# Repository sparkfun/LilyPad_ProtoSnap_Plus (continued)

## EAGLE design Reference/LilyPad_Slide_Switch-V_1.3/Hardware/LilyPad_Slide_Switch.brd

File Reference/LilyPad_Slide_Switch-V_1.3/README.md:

SparkFun LilyPad Slide Switch 
========================================

[*SparkFun LilyPad Slide Switch (DEV-09350)*](https://www.sparkfun.com/products/9350)

This is a simple slide switch for the LilyPad. 
Use it as a simple ON/OFF switch, or to control LEDs, buzzers, sensors, etc. The swtiches on each board are rated for 4 volts at 300mA, but will work at 5 volts with a reduction in current.

Repository Contents
-------------------

* **/Hardware** - Eagle design files (.brd, .sch)
* **/Production** - Production panel files (.brd)

Documentation
--------------

* **[Hookup Guide](https://learn.sparkfun.com/tutorials/ldk-experiment-3-buttons-and-switches)** - Basic hookup guide for the LilyPad Switch.
* **[SparkFun Fritzing repo](https://github.com/sparkfun/Fritzing_Parts)** - Fritzing diagrams for SparkFun products.
* **[SparkFun 3D Model repo](https://github.com/sparkfun/3D_Models)** - 3D models of SparkFun products. 

License Information
-------------------
This product is _**open source**_! 

The **hardware** is released under [Creative Commons ShareAlike 4.0 International](https://creativecommons.org/licenses/by-sa/4.0/).

Please use, reuse, and modify these files as you see fit. Please maintain attribution to SparkFun Electronics and release anything derivative under the same license.

Distributed as-is; no warranty is given.

- Your friends at SparkFun.

_Note: A portion of this sale is given back to Dr. Leah Buechley for continued development and education of e-textiles._

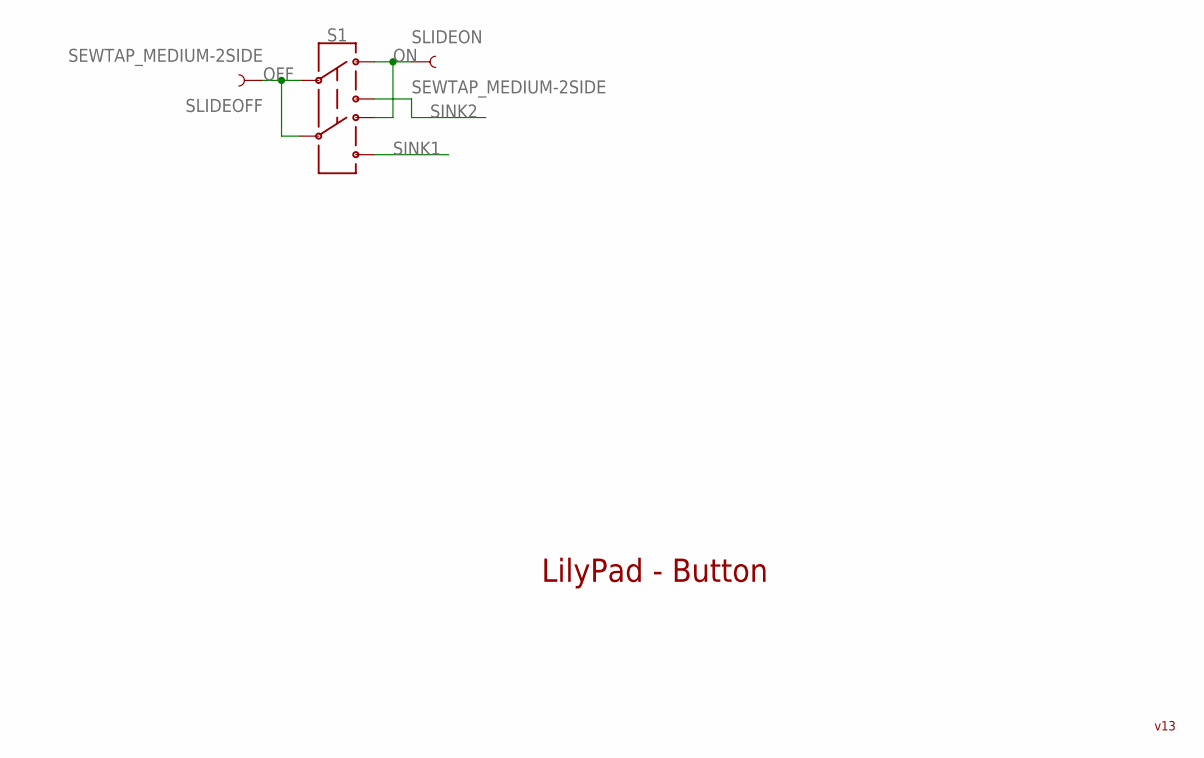
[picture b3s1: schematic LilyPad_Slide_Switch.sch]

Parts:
S1: SWITCH-DPDT-SMD-AYZ0202; SWITCH_DPDT_SMD_AYZ0202
SLIDEOFF: SEWTAP_MEDIUM-2SIDE; PETAL-MEDIUM-2SIDE
SLIDEON: SEWTAP_MEDIUM-2SIDE; PETAL-MEDIUM-2SIDE

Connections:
OFF: S1.2, S1.5, SLIDEOFF.1
ON: S1.1, S1.4, SLIDEON.1
SINK1: S1.6
SINK2: S1.3

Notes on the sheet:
LilyPad - Button
v13

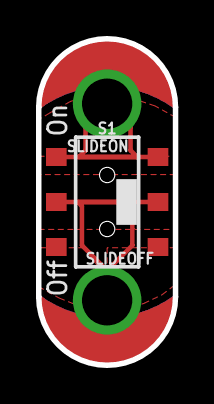
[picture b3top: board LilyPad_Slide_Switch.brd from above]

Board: 2 copper layers, 7.6 x 18.1 mm, 3 parts (0 on the bottom side), 2 nets.

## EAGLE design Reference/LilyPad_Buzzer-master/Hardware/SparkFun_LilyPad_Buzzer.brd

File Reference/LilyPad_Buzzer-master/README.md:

LilyPad Buzzer
========================================

[*LilyPad Buzzer (DEV-08463)*](https://www.sparkfun.com/products/8463)

This is a small buzzer for the LilyPad system. 
Use 2 I/O pins on the LilyPad main board and create different noises based on the different frequency of I/O toggling. 
Loud enough to hear inside a pocket but not obtrusively loud.

Repository Contents
-------------------

* **/Hardware** - Eagle design files (.brd, .sch)
* **/Production** - Production panel files (.brd)

Documentation
--------------
* **[SparkFun Fritzing repo](https://github.com/sparkfun/Fritzing_Parts)** - Fritzing diagrams for SparkFun products.
* **[SparkFun 3D Model repo](https://github.com/sparkfun/3D_Models)** - 3D models of SparkFun products. 

License Information
-------------------
This product is _**open source**_! 

The **hardware** is released under [Creative Commons ShareAlike 4.0 International](https://creativecommons.org/licenses/by-sa/4.0/).

Please use, reuse, and modify these files as you see fit. Please maintain attribution to SparkFun Electronics and release anything derivative under the same license.

Distributed as-is; no warranty is given.

- Your friends at SparkFun.

_**Note**: A portion of this sale is given back to Dr. Leah Buechley for continued development and education of e-textiles._

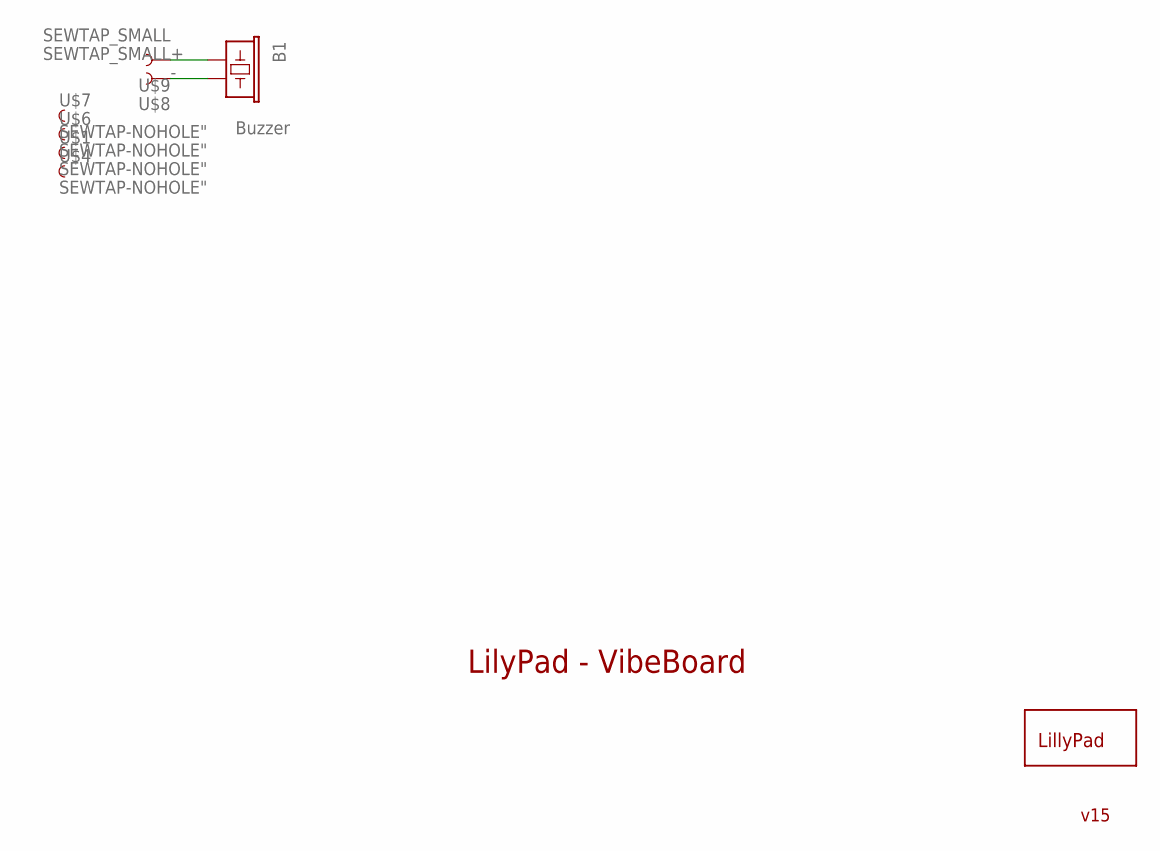
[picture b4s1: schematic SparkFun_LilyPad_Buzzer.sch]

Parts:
B1: Buzzer; BUZZER-CCV
U$1, U$4, U$6, U$7: SEWTAP-NOHOLE"; PETAL-NOHOLE
U$2: LOGO-LPLP; LOGO-LILYPAD
U$8, U$9: SEWTAP_SMALL; PETAL-SMALL

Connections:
+: B1.+ (1), U$9.1
-: B1.- (2), U$8.1

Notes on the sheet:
LilyPad - VibeBoard
v15

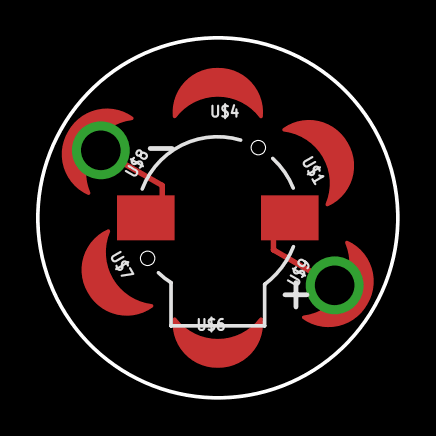
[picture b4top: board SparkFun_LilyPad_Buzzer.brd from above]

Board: 2 copper layers, 20.0 x 20.0 mm, 8 parts (1 on the bottom side), 2 nets.

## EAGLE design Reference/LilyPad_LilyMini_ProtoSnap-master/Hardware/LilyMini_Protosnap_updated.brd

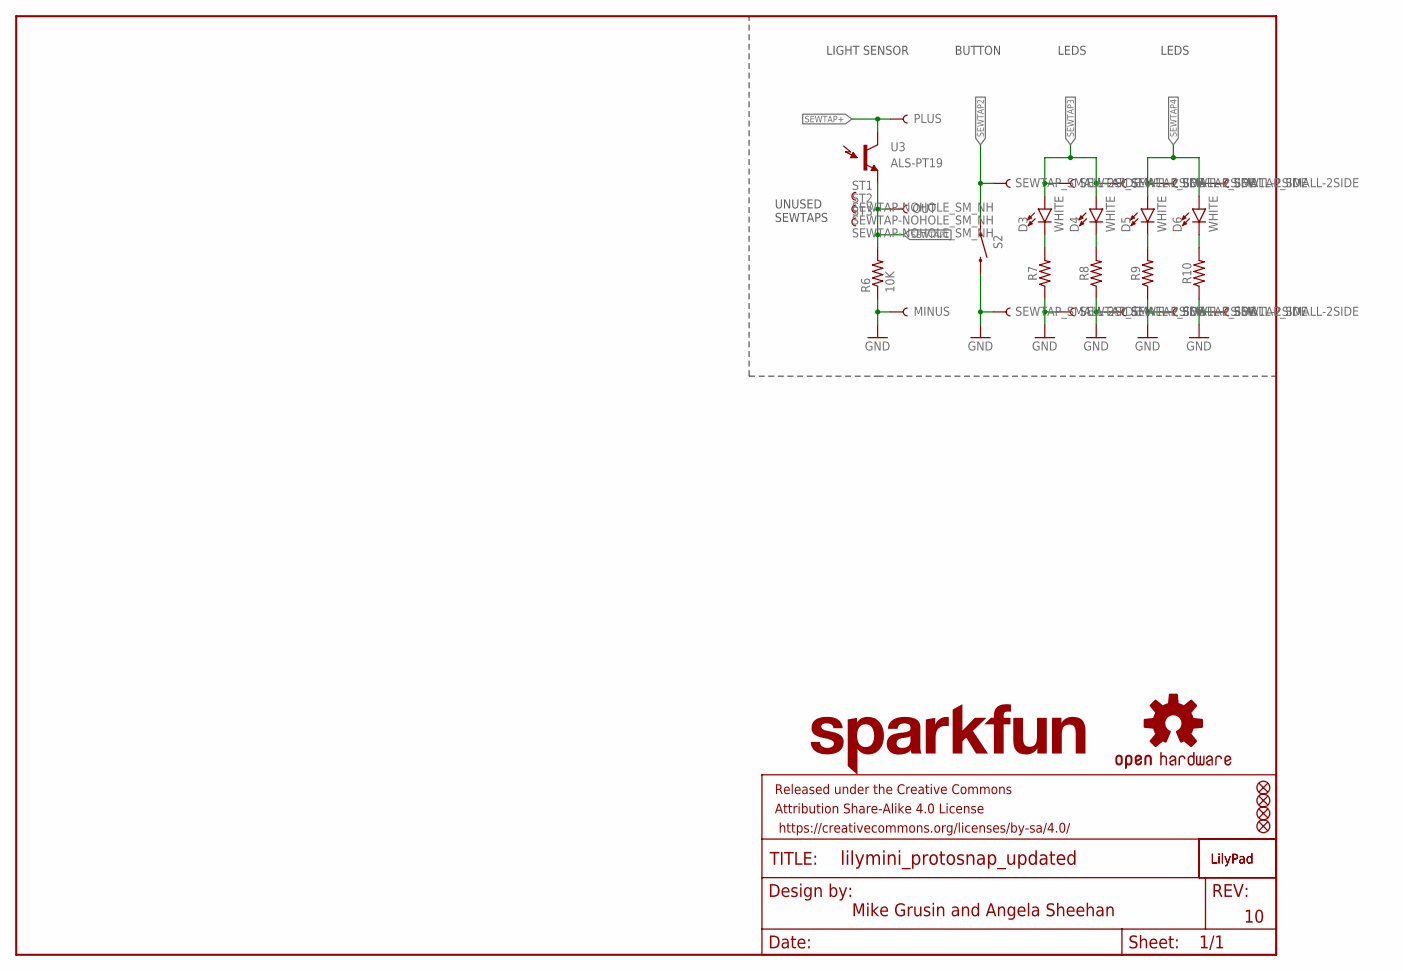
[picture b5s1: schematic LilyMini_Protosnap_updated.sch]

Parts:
$1_61_$_2016-09-25_21-56-09: OSHW-LOGOS; OSHW-LOGO-S
D3, D4, D5, D6: WHITE; LED-1206
FD1, FD2, FD3, FD4: FIDUCIAL1X2; FIDUCIAL-1X2
FRAME1: FRAME-LETTER; CREATIVE_COMMONS
JP12, JP13, JP20, JP21, JP22, JP23, JP24, JP25, JP26, JP27: SEWTAP_SMALL-2SIDE; PETAL-SMALL-2SIDE
LOGO1: LOGO-LPL; LOGO-L
LOGO2: LILYLOGO-L-TOP; LOGO-L-TOP
LOGO4: SFE_LOGO_NAME.1_INCH; SFE_LOGO_NAME_.1
R6: 10K; 0603-RES
R7, R8, R9, R10: 0603
S2: SWITCH-MOMENTARY-2SMD-REDUNDANT; TACTILE-SWITCH-SMD
SEWTAPLS+: PLUS; PETAL-SMALL-2SIDE
SEWTAPLS-: MINUS; PETAL-SMALL-2SIDE
SEWTAPLSOUT: OUT; PETAL-SMALL-2SIDE
ST1, ST2, ST3: SEWTAP-NOHOLE_SM_NH; PETAL-SMALL-NOHOLE
U3: ALS-PT19

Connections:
GND: JP13.1, JP21.1, JP23.1, JP25.1, JP27.1, R6.1, R7.1, R8.1, R9.1, R10.1, S2.3 (2), S2.4 (2), SEWTAPLS-.1
unnamed: D3.C, R7.2
unnamed: D4.C, R8.2
unnamed: D5.C, R9.2
unnamed: D6.C, R10.2
SEWTAP1: R6.2, SEWTAPLSOUT.1, U3.E (E1)
SEWTAP2: JP12.1, S2.1, S2.2 (1)
SEWTAP3: D3.A, D4.A, JP20.1, JP22.1
SEWTAP4: D5.A, D6.A, JP24.1, JP26.1
SEWTAP+: SEWTAPLS+.1, U3.C (C1)

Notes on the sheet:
UNUSED SEWTAPS
Mike Grusin and Angela Sheehan
LIGHT SENSOR
BUTTON
LEDS

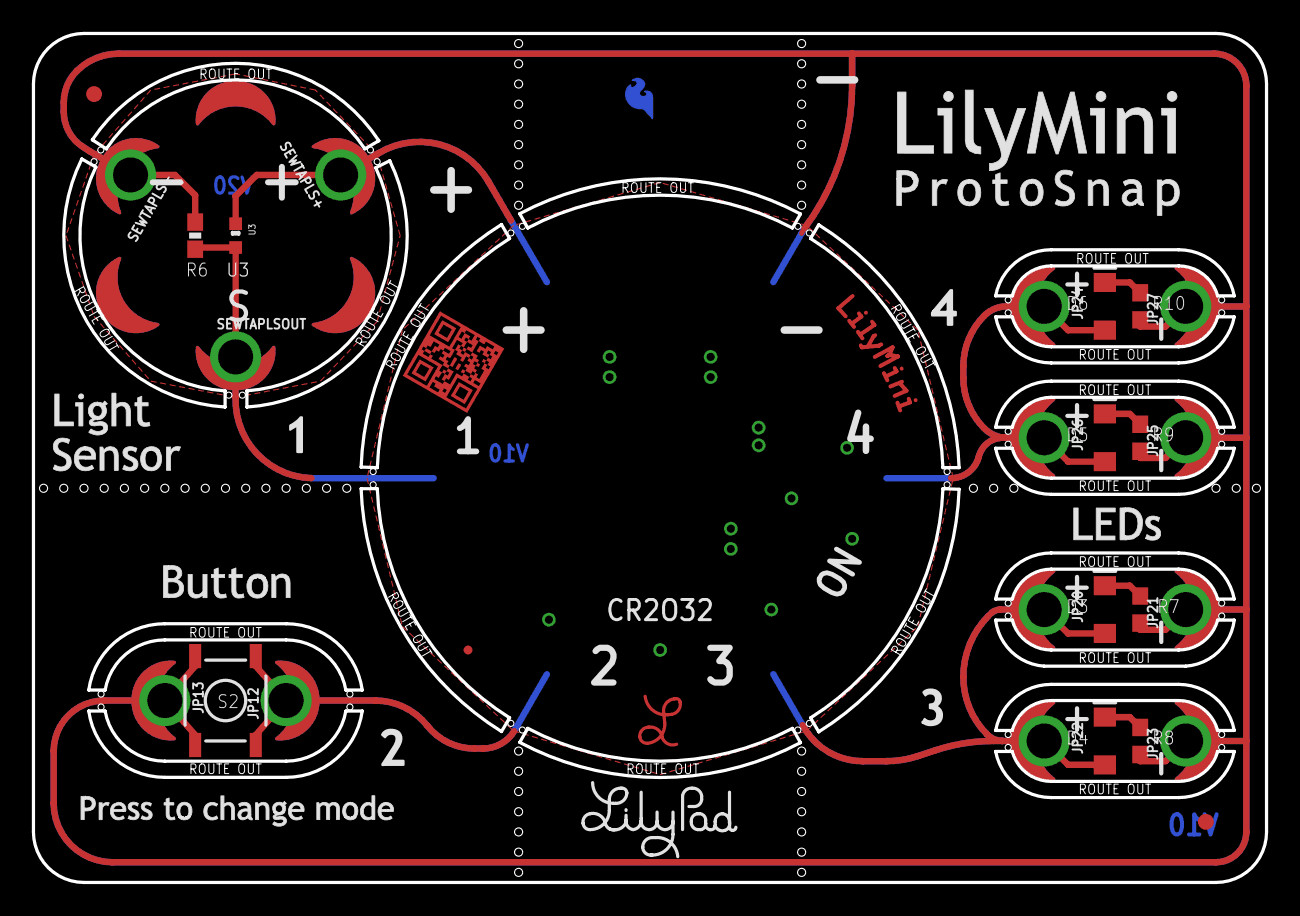
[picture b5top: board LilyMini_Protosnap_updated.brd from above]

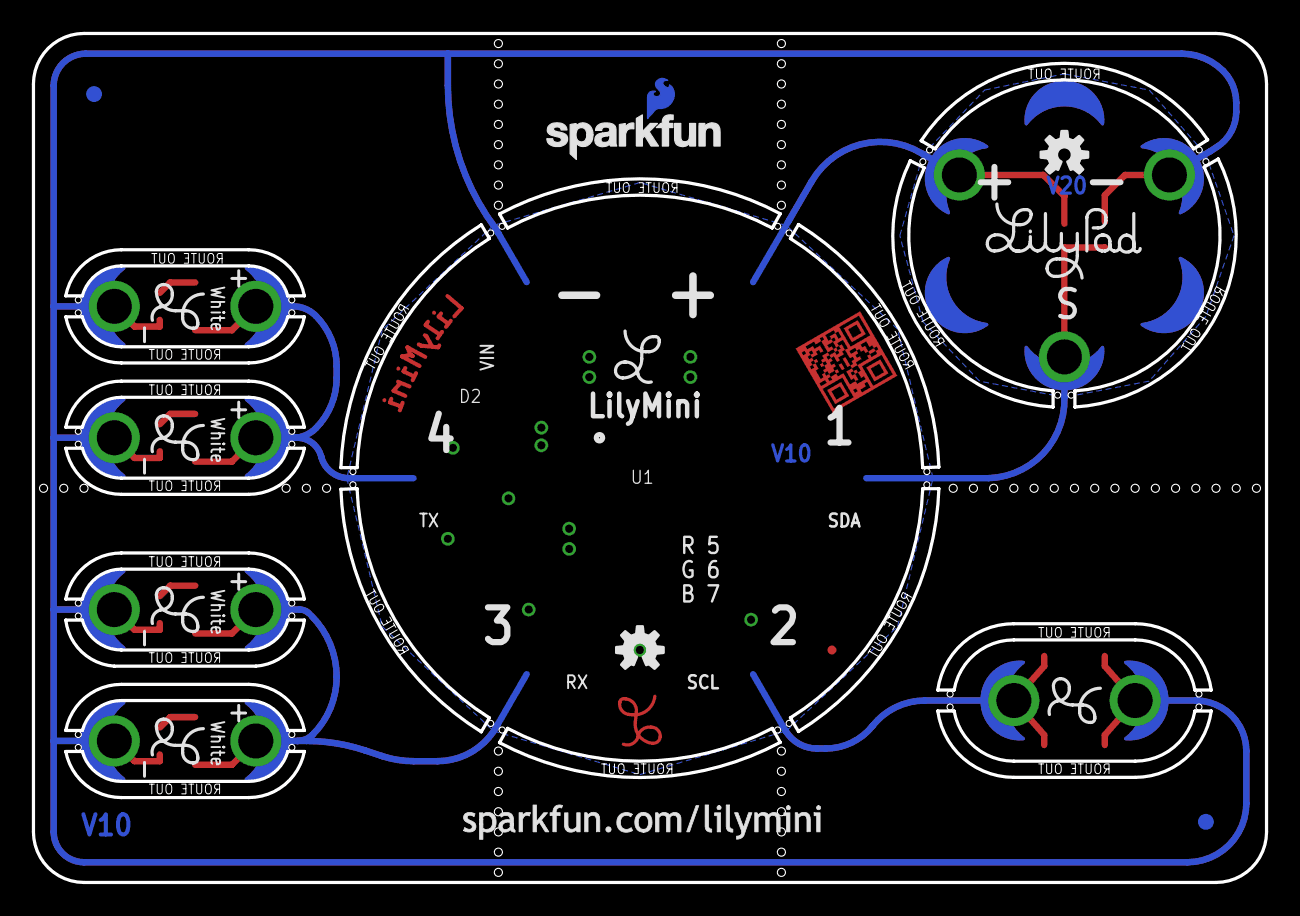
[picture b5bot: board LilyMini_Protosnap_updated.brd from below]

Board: 2 copper layers, 77.5 x 53.3 mm, 45 parts (13 on the bottom side), 10 nets.

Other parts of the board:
LOGO3: OSHW-LOGOS; OSHW-LOGO-S@1
U$1: LOGO-LILYPAD
U$2: LOGO-LPLP; LOGO-LILYPAD
U$4: SFE_LOGO_FLAME_COPPER_EXPOSED_.1
U$5, U$6, U$7, U$8, U$9: LOGO-L

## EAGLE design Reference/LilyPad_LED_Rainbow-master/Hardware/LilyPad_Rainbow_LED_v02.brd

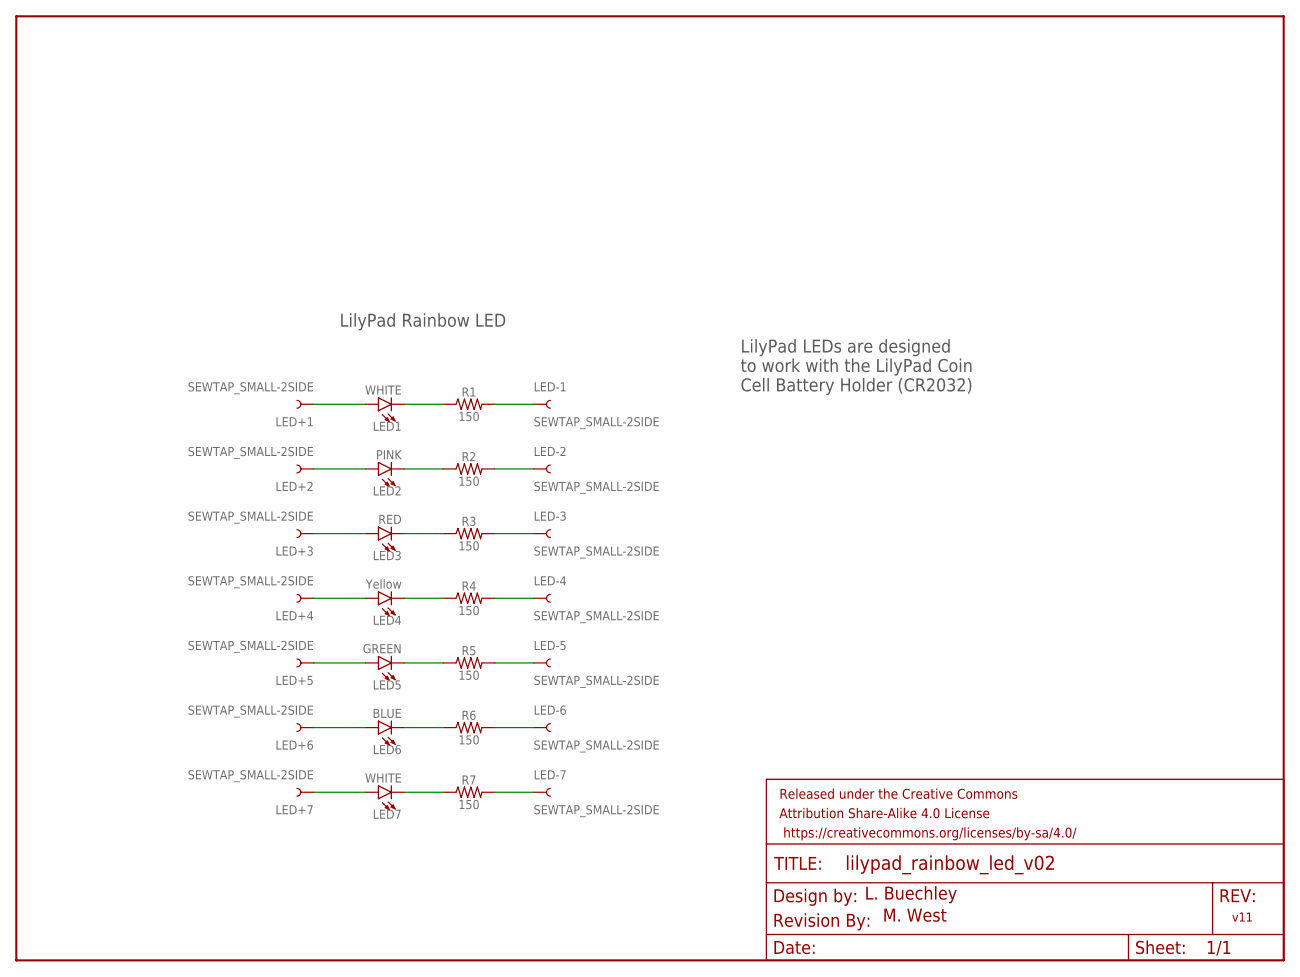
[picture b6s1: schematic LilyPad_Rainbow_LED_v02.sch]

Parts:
FRAME1: FRAME-LETTER; CREATIVE_COMMONS
LED1, LED7: WHITE; LED-1206
LED2: PINK; LED-1206
LED3: RED; LED-1206
LED4: Yellow; LED-1206
LED5: GREEN; LED-1206
LED6: BLUE; LED-1206
LED+1, LED+2, LED+3, LED+4, LED+5, LED+6, LED+7: SEWTAP_SMALL-2SIDE; PETAL-SMALL-2SIDE
LED-1, LED-2, LED-3, LED-4, LED-5, LED-6, LED-7: SEWTAP_SMALL-2SIDE; PETAL-SMALL-2SIDE
R1, R2, R3, R4, R5, R6, R7: 150; 0603
U$1: REVISION

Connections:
unnamed: LED1.A, LED+1.1
unnamed: LED1.C, R1.1
unnamed: LED-1.1, R1.2
unnamed: LED2.A, LED+2.1
unnamed: LED2.C, R2.1
unnamed: LED-2.1, R2.2
unnamed: LED3.A, LED+3.1
unnamed: LED3.C, R3.1
unnamed: LED-3.1, R3.2
unnamed: LED4.A, LED+4.1
unnamed: LED4.C, R4.1
unnamed: LED-4.1, R4.2
unnamed: LED5.A, LED+5.1
unnamed: LED5.C, R5.1
unnamed: LED-5.1, R5.2
unnamed: LED6.A, LED+6.1
unnamed: LED6.C, R6.1
unnamed: LED-6.1, R6.2
unnamed: LED7.A, LED+7.1
unnamed: LED7.C, R7.1
unnamed: LED-7.1, R7.2

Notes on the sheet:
L. Buechley
M. West
v11
LilyPad Rainbow LED
LilyPad LEDs are designed to work with the LilyPad Coin Cell Battery Holder (CR2032)

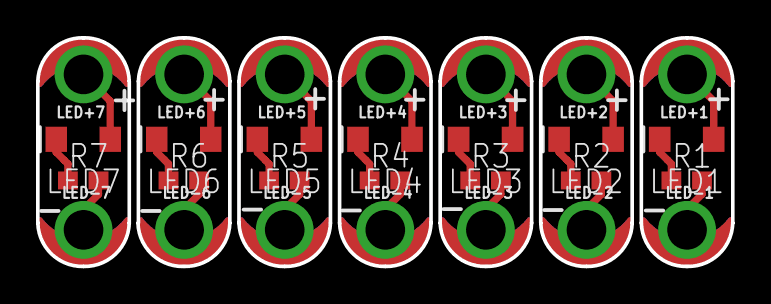
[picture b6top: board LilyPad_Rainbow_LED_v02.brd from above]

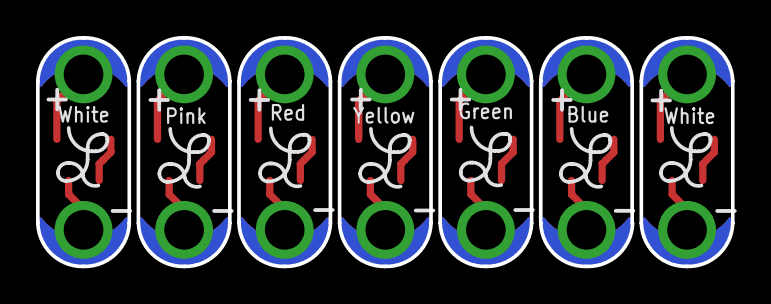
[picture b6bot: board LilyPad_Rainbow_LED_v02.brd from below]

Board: 2 copper layers, 38.6 x 12.7 mm, 37 parts (7 on the bottom side), 21 nets.

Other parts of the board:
LOGO29, LOGO30, LOGO31, LOGO32, LOGO33, LOGO34, LOGO35: LOGO-LPL; LOGO-L

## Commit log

2017-06-08 Center (mcu) board complete
2017-06-13 v35 ready for initial review
2017-06-14 Almost ready for review. Art has been finalized
2017-06-14 Ready for review
2017-06-14 Added part number to RGB led
2017-06-14 Tweaked a couple resistor values
2017-06-14 Fixed some stop/lilypad tab errors
2017-06-15 Addressed DFM errors
2017-06-15 Added extra test points
2017-06-16 Moved lilypad logo to dodge connector, created v01 gerbers
2017-06-20 Adjusted routes, drills, and USB connector for PCB fab house requirements, incremented design to v03
2017-06-26 Added misplaced part to local library
2017-08-15 Implemented most physical changes from proto 1
2017-08-16 More proto changes in
2017-08-16 Added pth/npth notes
2017-08-17 Imported new silk
    Replaced name and major labeling with polygons derived from Trebuchet
    font (LilyPad standard). Polarity and internal labeling left in Eagle
    vector font.
2017-08-21 Added changes from reds review
2017-08-21 Ran engineering checklist
2017-08-22 Updated reds QC check
2017-08-22 Removed d2 90
2017-08-23 Fixed bad holes, mask issue
2017-08-24 panel
2017-09-25 Fixed spelling error
2017-09-26 Updated documentation in preparation for release
2017-10-02 Changed bargraph resistors to 470 ohm
    To reduce brightness of white LED bargraph, changed R8-R13 inclusive
    from 22 ohm to 470 ohm 0402 RES-13829 (new part)
2017-10-05 Update README.md
    Link image to product.
2017-10-05 Update README.md
    - Add Tutorial Link.
    - Remove:
    * **[Library](GitHub library URL)** - <LANGUAGE> library for the <PRODUCT NAME>.
    * **[SparkFun Fritzing repo](https://github.com/sparkfun/Fritzing_Parts)** - Fritzing diagrams for SparkFun products.
    * **[SparkFun 3D Model repo](https://github.com/sparkfun/3D_Models)** - 3D models of SparkFun products.
    * **[SparkFun Graphical Datasheets](https://github.com/sparkfun/Graphical_Datasheets)** -Graphical Datasheets for various SparkFun products.
2017-10-06 Update README.md
    Removing section about the Repository Contents:
    * **/Firmware** - Example code
    We will be eventually adding a note to with the default example code in another repository in the future.
2017-12-08 Update README.md
    Adding additional example code repository.
2017-12-08 Update README.md
    Adding additional product versions.
2018-01-11 Added software serial doc
2018-01-12 Testing driver
